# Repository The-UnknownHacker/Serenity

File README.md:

# Serenity

**Serenity** is a drumpad or macropad designed with musicians in mind.  
Instead of using traditional switches or buttons, it uses a **copper layer on the PCB** to detect touch input.

Powered by an **ESP32-S3 devkit**, Serenity can store sound files on a **microSD card** and output audio through a **headphone jack**.

It features **2 configurable buttons** that let you switch between sound "layers" — allowing you to play many more sounds than just 8.  
For example, with 4 layers, you can trigger **32 unique sounds**.

---

I built **Serenity** after being inspired by those expensive drumpads used for triggering sound effects.  
They often cost a fortune, so I created **Serenity** to cost **under $50 USD**, without sacrificing creativity or functionality.
=======

Images

-------------
Schematic

PCB

3D Model

BOM

| Designator | Footprint | Quantity | Value | LCSC Part # | Purchase Method | Est. Price (USD) |
|------------|-----------|----------|-------|-------------|-----------------|-------------------|
| C1 | 1812 | 1 | 100nf | https://lcsc.com/product-detail/Multilayer-Ceramic-Capacitors-MLCC-SMD-SMT_TDK_C342613.html | PCBA | $0.34 |
| J1 | microSD_HC_Molex_47219-2001 | 1 | Micro_SD_Card | https://lcsc.com/product-detail/SD-Card-Memory-Card-Connector_MOLEX-472192001_C164170.html | PCBA | $0.48 |
| J2 | HRO_PJ-320D-A | 1 | PJ-320D-A | https://lcsc.com/product-detail/_Korean-Hroparts-Elec-PJ-320D-4A_C95562.html | PCBA | $1.50* |
| SW1, SW2 | SW_PUSH-12mm_Wuerth-430476085716 | 2 | SW_Push | https://www.adafruit.com/product/1119?srsltid=AfmBOoqwRE8KhgtdWcEbSr0UxHVauoeQpAy56lpgwJ67pl_6lD0DS_sJ | Ordering Online | $2.50* |
| U1 | ESP32-S2-DevKitC-1 | 1 | ESP32-S3-DevKitC | https://www.aliexpress.com/item/1005006446406795.html?src=google&pdp_npi=4%40dis!AUD!26.47!8.19!!!!!%40!12000037200113934!ppc!!!&snpsid=1&snps=y&src=google&albch=shopping&acnt=708-803-3821&isdl=y&slnk=&plac=&mtctp=&albbt=Google_7_shopping&aff_platform=google&aff_short_key=UneMJZVf&gclsrc=aw.ds&&albagn=888888&&ds_e_adid=&ds_e_matchtype=&ds_e_device=c&ds_e_network=x&ds_e_product_group_id=&ds_e_product_id=en1005006446406795&ds_e_product_merchant_id=5551326180&ds_e_product_country=AU&ds_e_product_language=en&ds_e_product_channel=online&ds_e_product_store_id=&ds_url_v=2&albcp=19366639602&albag=&isSmbAutoCall=false&needSmbHouyi=false&gad_source=1&gad_campaignid=17338734196&gbraid=0AAAAAD6I-hFKAadTE4Avff5KRQWZAVIR1&gclid=Cj0KCQjwmqPDBhCAARIsADorxIYCUFoJhmIURqGGyT1Bnp1HNg7o4UZPdnUgz-yrKNdseuVaICe9NbkaAqTaEALw_wcB | Ordering Online | $10.00 |
| U2 | TQFN-16-1EP_3x3mm_P0.5mm_EP1.23x1.23mm | 1 | MAX98357A | https://lcsc.com/product-detail/Audio-Amplifiers_Analog-Devices-Inc-Maxim-Integrated-MAX98357AETE-T_C910544.html?s_z=n_MAX98357AETE%2BT | PCBA | $3.50* |

## Total Estimated Cost
**Subtotal: ~$50 USD** without shipping

- Prices dont include shipping, taxes, and PCBA assembly fees
- PCBA components might have additional assembly costs

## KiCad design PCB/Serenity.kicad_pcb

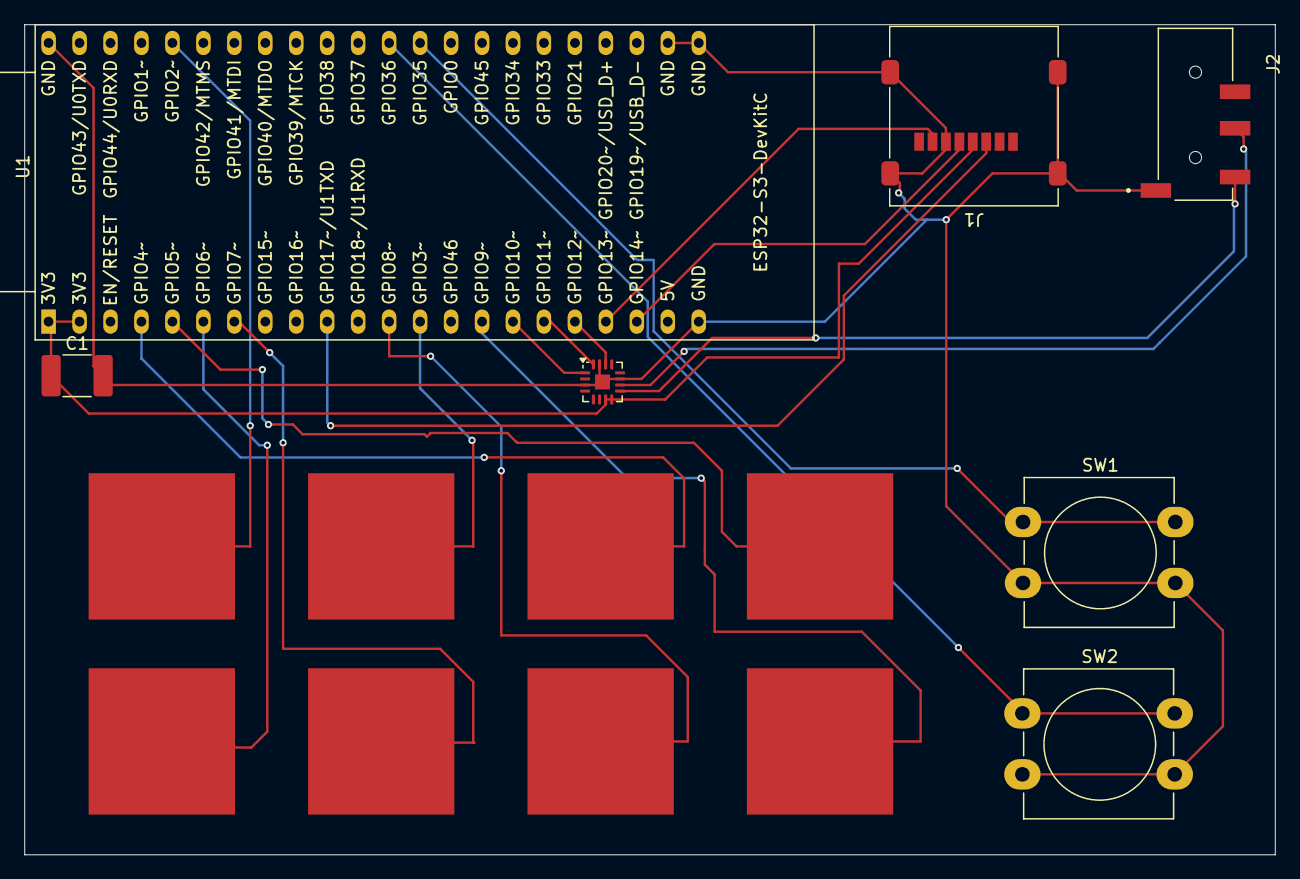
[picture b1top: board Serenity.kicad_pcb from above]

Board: 2 copper layers, 102.6 x 68.1 mm, 7 parts (0 on the bottom side), 12 nets.

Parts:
C1: 100nf; C_1812_4532Metric_Pad1.57x3.40mm_HandSolder
J1: Micro_SD_Card; microSD_HC_Molex_47219-2001
J2: PJ-320D-A; HRO_PJ-320D-A
SW1, SW2: SW_Push; SW_PUSH-12mm_Wuerth-430476085716
U1: ESP32-S3-DevKitC; ESP32-S2-DevKitC-1
U2: MAX98357A; TQFN-16-1EP_3x3mm_P0.5mm_EP1.23x1.23mm

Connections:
BCLK: U1.17 (GPIO11/ADC2_CH0), U2.16 (BCLK)
CLK: J1.5 (CLK), U1.20 (GPIO14/ADC2_CH3)
CMD: J1.3 (CMD), U1.10 (GPIO17/ADC2_CH6)
DAT0: J1.7 (DAT0), U1.19 (GPIO13/ADC2_CH2)
DIN: U1.16 (GPIO10/ADC1_CH9), U2.1 (DIN)
GPIO35: SW1.1, U1.32 (GPIO35)
GPIO36: SW2.1, U1.33 (GPIO36)
LRCLK: U1.18 (GPIO12/ADC2_CH1), U2.14 (LRCLK)
RING: J2.3, U2.10 (OUTN)
TIP: J2.2, U2.9 (OUTP)
VDD: C1.1, J1.4 (VDD), U1.1 (3V3), U1.2 (3V3), U2.7 (VDD), U2.8 (VDD)
VSS: C1.2, J1.6 (VSS), J1.9 (SHIELD), J2.1, SW1.2, SW2.2, U1.22 (GND), U1.23 (GND), U1.24 (GND), U1.44 (GND), U2.3 (GND), U2.11 (GND), U2.15 (GND), U2.17 (PAD)

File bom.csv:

Designator,Footprint,Quantity,Value,LCSC Part #,Purchase Method
C1,1812,1,100nf,https://lcsc.com/product-detail/Multilayer-Ceramic-Capacitor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,PCBA
J1,microSD_HC_Molex_47219-2001,1,Micro_SD_Card,https://lcsc.com/product-detail/SD-Card-Memory-Card-Connecto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,PCBA
J2,HRO_PJ-320D-A,1,PJ-320D-A,https://lcsc.com/product-detail/_Korean-Hroparts-Elec-PJ-320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,PCBA
"SW1, SW2",SW_PUSH-12mm_Wuerth-430476085716,2,SW_Push,https://www.adafruit.com/product/1119?srsltid=AfmBOoqwRE8Khg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,Ordering Online
U1,ESP32-S2-DevKitC-1,1,ESP32-S3-DevKitC,https://www.altronics.com.au/p/z6433-esp-32s3-development-bo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,Going Inshore (Local Shop)
U2,TQFN-16-1EP_3x3mm_P0.5mm_EP1.23x1.23mm,1,MAX98357A,https://lcsc.com/product-detail/Audio-Amplifiers_Analog-Devi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,
